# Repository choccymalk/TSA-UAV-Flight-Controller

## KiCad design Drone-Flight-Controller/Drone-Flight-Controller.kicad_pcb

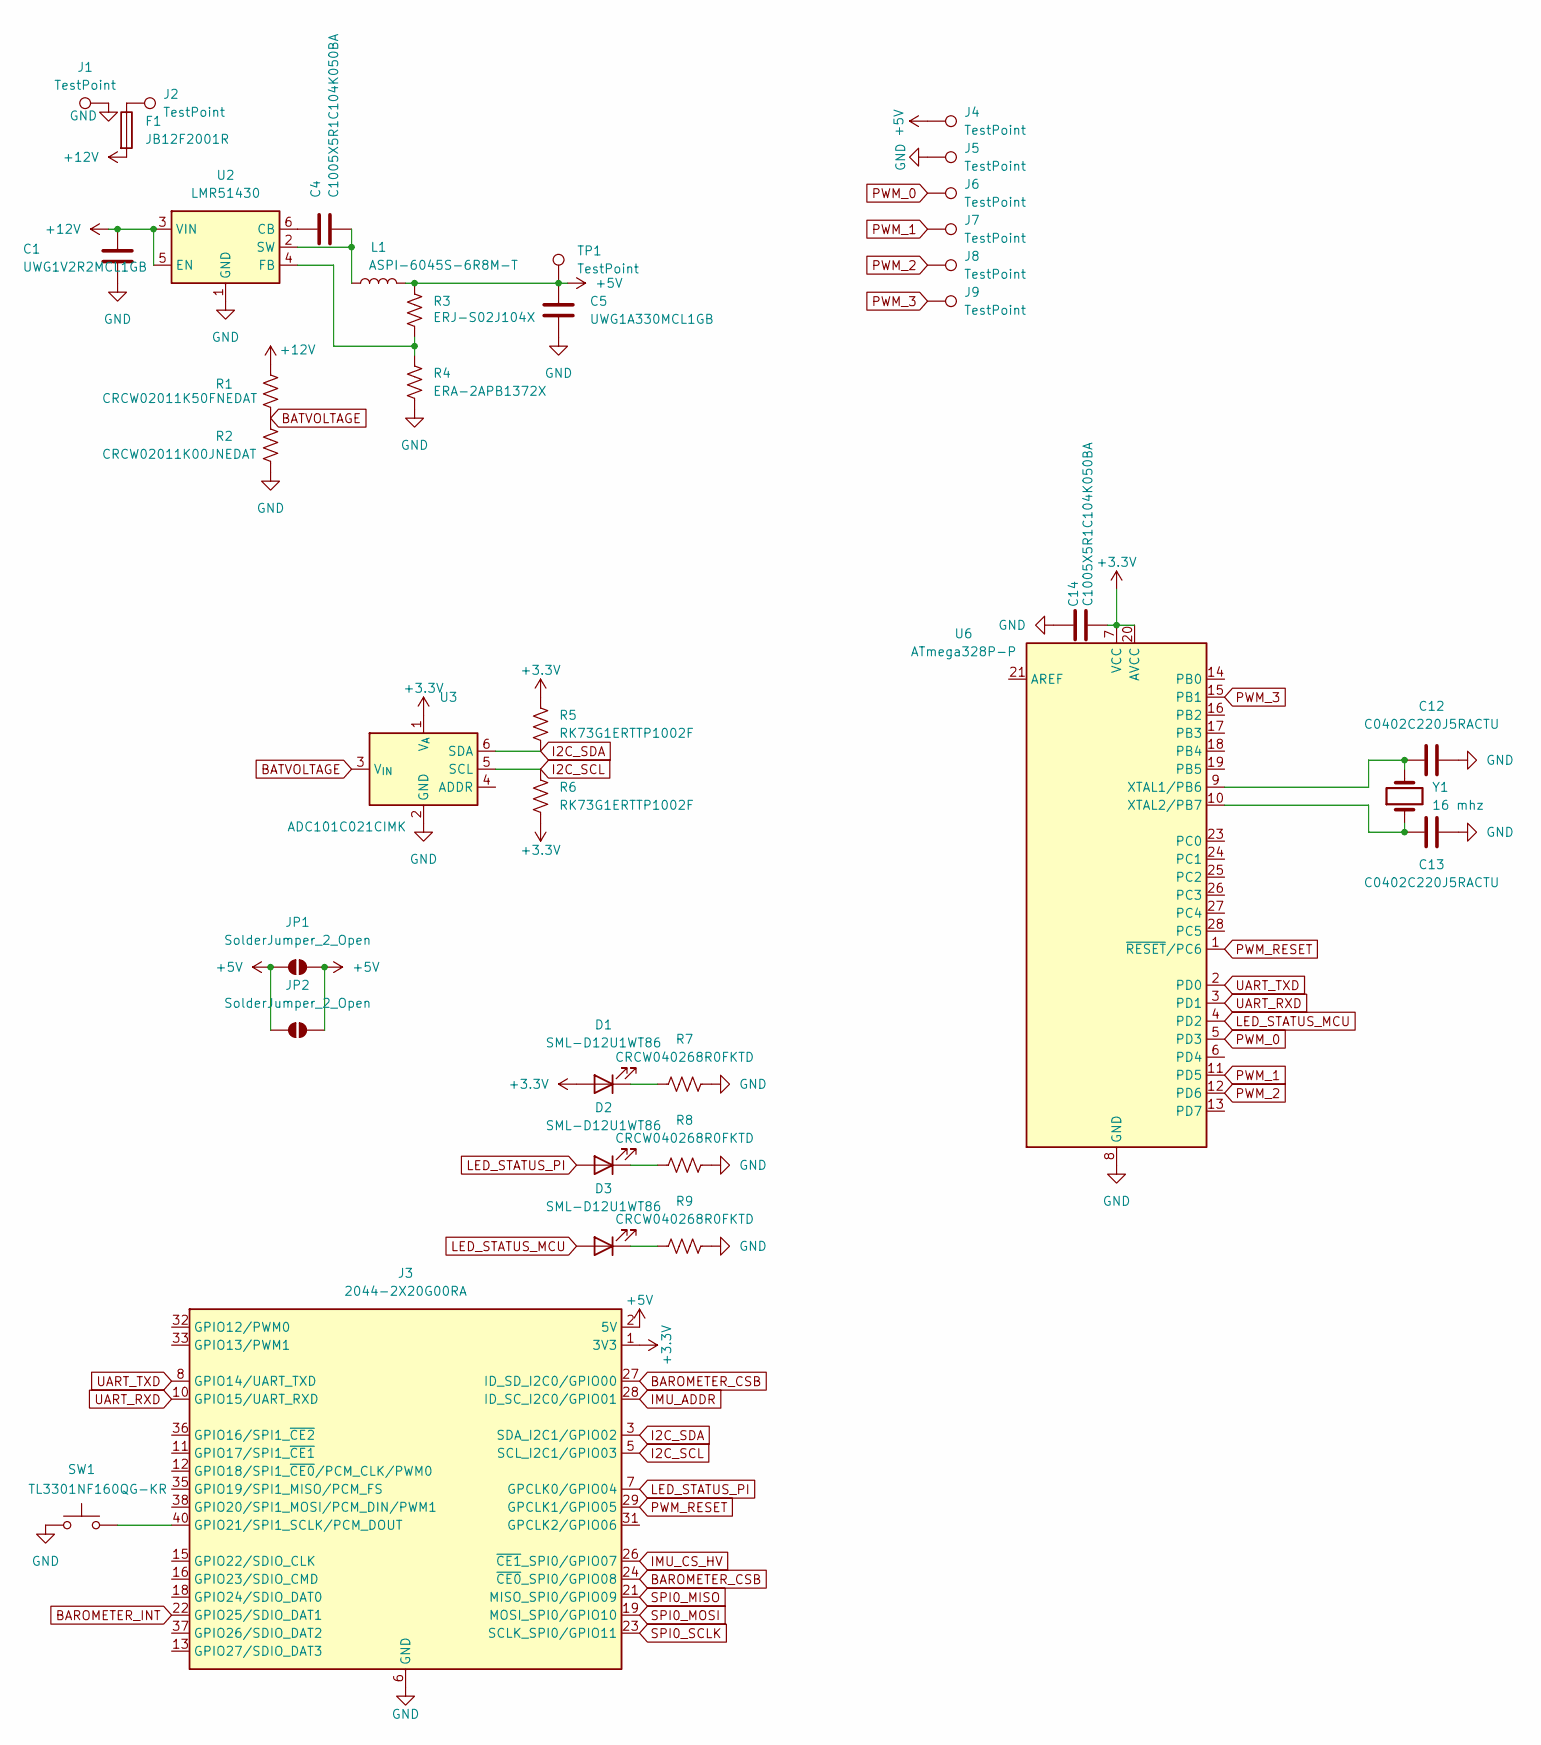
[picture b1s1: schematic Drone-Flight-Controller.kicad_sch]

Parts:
C1: UWG1V2R2MCL1GB; C_Elec_4x5.4
C4, C14: C1005X5R1C104K050BA; C_0402_1005Metric
C5: UWG1A330MCL1GB; C_Elec_5x5.4
C12, C13: C0402C220J5RACTU; C_0402_1005Metric
D1, D2, D3: SML-D12U1WT86; LED_0603_1608Metric
F1: JB12F2001R; Fuse_1206_3216Metric
J1, J2, J4, J5, J6, J7, J8, J9: TestPoint; TestPoint_Pad_D2.0mm
J3: 2044-2X20G00RA; PinSocket_2x20_P2.54mm_Vertical
JP1, JP2: SolderJumper_2_Open; SolderJumper-2_P1.3mm_Open_Pad1.0x1.5mm
L1: ASPI-6045S-6R8M-T; L_1812_4532Metric
R1: CRCW02011K50FNEDAT; R_0402_1005Metric
R2: CRCW02011K00JNEDAT; R_0402_1005Metric
R3: ERJ-S02J104X; R_0402_1005Metric
R4: ERA-2APB1372X; R_0402_1005Metric
R5, R6: RK73G1ERTTP1002F; R_0402_1005Metric
R7, R8, R9: CRCW040268R0FKTD; R_0402_1005Metric
SW1: TL3301NF160QG-KR; SW_Push_1P1T_NO_CK_KMR2
TP1: TestPoint; TestPoint_Pad_D2.0mm
U2: LMR51430; SOT-23-6
U3: ADC101C021CIMK; SOT-23-6
U6: ATmega328P-P; DIP-28_W7.62mm
Y1: 16 mhz; Crystal_SMD_Abracon_ABM3-2Pin_5.0x3.2mm

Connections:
+3.3V: C14.1, D1.2 (A), J3.1 (3V3), J3.17 (3V3), R5.1, R6.2, U3.1 (V_{A}), U6.7 (VCC), U6.20 (AVCC)
+5V: C5.1, J3.2 (5V), J3.4 (5V), J4.1, JP1.1 (A), JP1.2 (B), JP2.1 (A), JP2.2 (B), L1.2, R3.1, TP1.1
+12V: C1.1, F1.2, R1.1, U2.3 (VIN), U2.5 (EN)
BAROMETER_CSB: J3.24 (~CE0_SPI0/GPIO08), J3.27 (ID_SD_I2C0/GPIO00)
BAROMETER_INT: J3.22 (GPIO25/SDIO_DAT1)
BATVOLTAGE: R1.2, R2.1, U3.3 (V_{IN})
GND: C1.2, C5.2, C12.2, C13.2, C14.2, J1.1, J3.6 (GND), J3.9 (GND), J3.14 (GND), J3.20 (GND), J3.25 (GND), J3.30 (GND), J3.34 (GND), J3.39 (GND), J5.1, R2.2, R4.2, R7.2, R8.2, R9.2, SW1.1, U2.1 (GND), U3.2 (GND), U6.8 (GND), U6.22 (GND)
I2C_SCL: J3.5 (SCL_I2C1/GPIO03), R6.1, U3.5 (SCL)
I2C_SDA: J3.3 (SDA_I2C1/GPIO02), R5.2, U3.6 (SDA)
IMU_ADDR: J3.28 (ID_SC_I2C0/GPIO01)
IMU_CS_HV: J3.26 (~CE1_SPI0/GPIO07)
LED_STATUS_MCU: D3.2 (A), U6.4 (PD2)
LED_STATUS_PI: D2.2 (A), J3.7 (GPCLK0/GPIO04)
unnamed: D1.1 (K), R7.1
unnamed: D2.1 (K), R8.1
unnamed: D3.1 (K), R9.1
unnamed: F1.1, J2.1
unnamed: J3.40 (GPIO21/SPI1_SCLK/PCM_DOUT), SW1.2
unnamed: C4.1, U2.6 (CB)
unnamed: R3.2, R4.1, U2.4 (FB)
unnamed: C4.2, L1.1, U2.2 (SW)
unnamed: C12.1, U6.9 (XTAL1/PB6), Y1.2
unnamed: C13.1, U6.10 (XTAL2/PB7), Y1.1
PWM_0: J6.1, U6.5 (PD3)
PWM_1: J7.1, U6.11 (PD5)
PWM_2: J8.1, U6.12 (PD6)
PWM_3: J9.1, U6.15 (PB1)
PWM_RESET: J3.29 (GPCLK1/GPIO05), U6.1 (~RESET/PC6)
SPI0_MISO: J3.21 (MISO_SPI0/GPIO09)
SPI0_MOSI: J3.19 (MOSI_SPI0/GPIO10)
SPI0_SCLK: J3.23 (SCLK_SPI0/GPIO11)
UART_RXD: J3.10 (GPIO15/UART_RXD), U6.3 (PD1)
UART_TXD: J3.8 (GPIO14/UART_TXD), U6.2 (PD0)

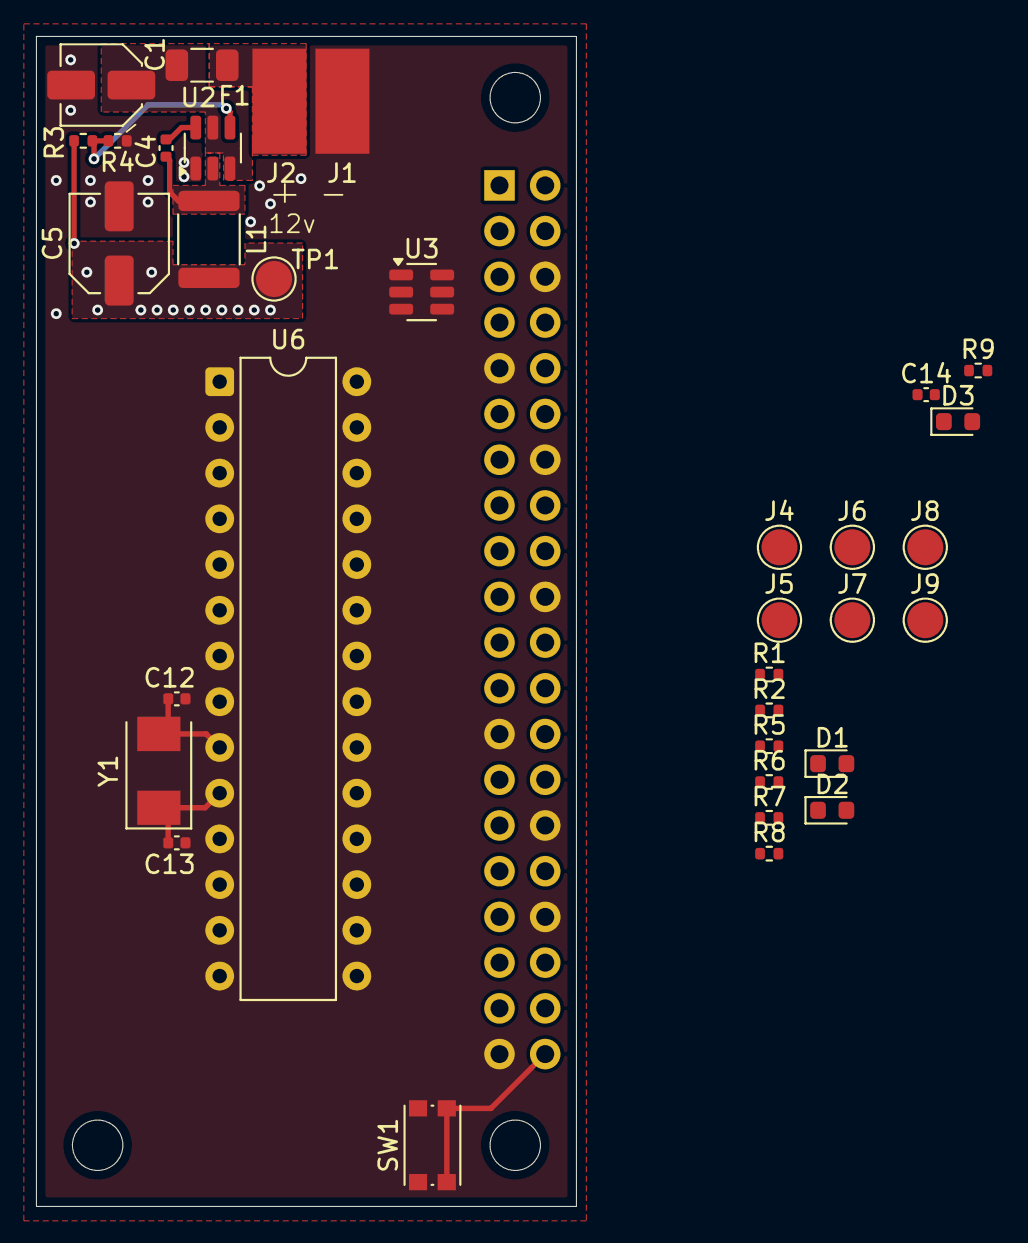
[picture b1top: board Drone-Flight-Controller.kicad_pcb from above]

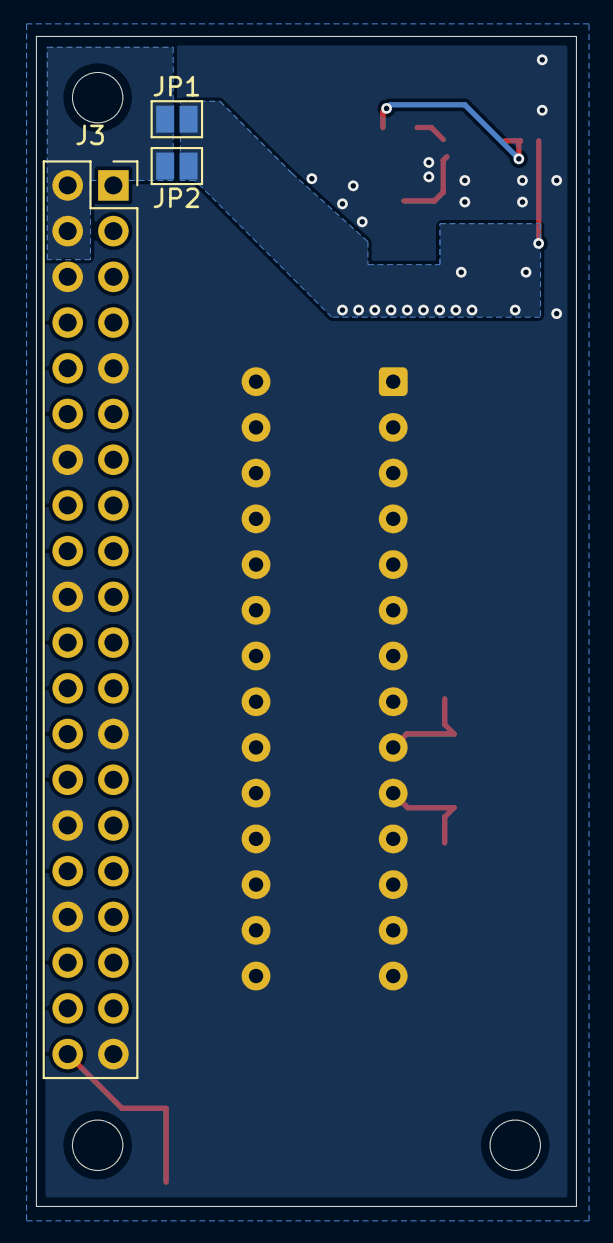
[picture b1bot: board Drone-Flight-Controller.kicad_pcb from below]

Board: 2 copper layers, 30.0 x 65.0 mm, 37 parts (3 on the bottom side), 27 nets.

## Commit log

2025-10-25 add atmega328p based controller
2025-10-27 move to stm32
2025-10-27 forgot to save
2025-10-30 move to more powerful mcu
2025-10-31 laid out pcb with new mcu
2025-10-31 remove third and fourth layer traces
2025-11-05 remove stm32
    processing will be done on the rpi now
2025-11-05 pin header is female and on the bottom now
2025-11-06 change imu to one that isnt eol
2025-11-06 add a fuse
2025-11-07 put fuse on pcb
2025-11-07 move imu to center of pcb
2025-11-10 added imu level shifter
2025-11-11 optimized routing
2025-11-13 connect imu and barometer to spi0
2025-11-14 switch to bmp390 for barometer
    bmp280 isnt being stocked at digikey or mouser anymore
2025-11-19 i2c to pwm is now a pca9685
2025-12-02 level shifters are a single part now
2025-12-05 add code for the arduino side and start rpi side
2025-12-06 change serial comm protocol
2025-12-06 fix serial protocol
2025-12-06 fix bugs
2025-12-06 forgot to add index.html
2025-12-06 add option to get parsed data
2025-12-06 add a gitignore and try to fix main.cpp
2025-12-06 add timestamps to error messages
2025-12-06 fix communication
2025-12-06 add a way to send serial data
2025-12-06 the arduino now has to be asked for data
2025-12-06 make index.html more user friendly
2025-12-07 receivecontrol happens before anything else now
2025-12-07 websockets!
2025-12-07 optimize serial communication
2025-12-07 reduce refresh rate for the ws connection
2025-12-07 add a camera stream
2025-12-08 fix cmakelists.txt
2025-12-08 fix cmakelists.txt again
2025-12-08 optimization
2025-12-09 more optimization
2025-12-15 add overlaid simulated horizon to video stream
